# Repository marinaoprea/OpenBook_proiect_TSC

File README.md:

### ESP32-C6 pin connections
* 3V3 - charging 3V3
* EN - Reset button
* IO0 - pin for communication with the RTC (to get alert or timing signals)
* IO1 - pin used to communicate with the RTC to get a stable clock reference
* IO2 - used for SPI (Master In Slave Out)
* IO3 - used to connect to display, indicates the display's busy status
* IO4 - used to communicate with the SD card
* IO5 - used to connect to the display, distinguishes between data and command signals sent to
        to the display
* IO6 - used for SPI communication, synchronizes data transfer
* IO7 - used for SPI (Master Out Slave In)
* IO8 - not used
* IO9 - Boot button
* IO10 - used to connect to the display, selects the display for communication
* IO11 - selects the flash memory for communication
* IO12 - D+ for USB connection
* IO13 - D- for USB connection
* IO15 - Change button
* TXd0 / GPIO16 - used for UART debugging
* RXD0/GPIO17 - used for UART debugging
* IO18 - resets RTC
* IO19 - power pin for I2C communication
* IO20 - power for display
* IO21 - used for I2C, data pin
* IO22 - used for I2C, clock pin
* IO23 - resets display
* GND - connected to GND

### Bill of Materials

| Part | Value | Datasheet Link | Buy Link
|:------|:-------|:----------------|:---------------|
| BOOT_BUTTON | BUTTON_CUSYOMV1 | [Datasheet](https://www3.panasonic.biz/ac/e_download/control/switch/light-touch/catalog/sw_lt_eng_6s_th.pdf?f_cd=402892) | [Buy](https://ro.mouser.com/ProductDetail/Panasonic/EVQ-PUJ02K?qs=Pa1bP%252BeMzadWe338tXJdGA%3D%3D&utm_id=6470900573&utm_source=google&utm_medium=cpc&utm_marketing_tactic=emeacorp&gad_source=1&gclid=CjwKCAjwzMi_BhACEiwAX4YZULlhUyQwmA3c7mdDUuSFCAo9XeR8UBKFF0gyZe49KYTmnIC5sRRx0RoCqN8QAvD_BwE)
| C1 | 100nF | [Datasheet](https://ro.mouser.com/datasheet/2/447/KEM_C1006_X5R_SMD-3316465.pdf) | [Buy](https://ro.mouser.com/ProductDetail/YAGEO/CC0402MRX5R5BB106?qs=zEY9bCHj09eCmUJdZuS5Lg%3D%3D&utm_id=6470900573&utm_source=google&utm_medium=cpc&utm_marketing_tactic=emeacorp&gad_source=1&gclid=CjwKCAjwzMi_BhACEiwAX4YZUH3AaP6uvHGdYeUYb7BO2eMjk8ZR0XihcHuw-sWwNUHwSShuLip--hoCBnYQAvD_BwE)
| C1_BAT | 4.7uF | [Datasheet](https://ro.mouser.com/datasheet/2/447/KEM_C1006_X5R_SMD-3316465.pdf) | [Buy](https://ro.mouser.com/ProductDetail/YAGEO/CC0402MRX5R5BB106?qs=zEY9bCHj09eCmUJdZuS5Lg%3D%3D&utm_id=6470900573&utm_source=google&utm_medium=cpc&utm_marketing_tactic=emeacorp&gad_source=1&gclid=CjwKCAjwzMi_BhACEiwAX4YZUH3AaP6uvHGdYeUYb7BO2eMjk8ZR0XihcHuw-sWwNUHwSShuLip--hoCBnYQAvD_BwE)
| C1_BAT1 | 4.7uF |  |
| C1_BAT2 | 4.7uF |  |
| C2 | 100nF |  |
| C2_BAT | 4.7uF |  |
| C3 | 100uF TANT |  |
| C4 | 4.7uF/25V |  |
| C4_USB | 100nF |  |
| C5 | 1uF |  |
| C5_USB | 4.7uF |  |
| C6 | 100nF |  |
| C7 | 10uF |  |
| C8 | 100nF |  |
| C9 | 100nF |  |
| C10 | 100nF |  |
| C10_SUPERCAP | | [Datasheet](https://www.snapeda.com/parts/CPH3225A/Seiko+Instruments/view-part/?ref=eda) | [Buy](https://www.digikey.ro/en/products/detail/seiko-instruments/CPH3225A/8692444?utm_campaign=buynow&utm_medium=aggregator&utm_source=snapeda)
| CHANGE_BUTTON BUTTON_CUSYOMV1 | |  |
| CHG_LED | |[Datasheet](https://dammedia.osram.info/media/resource/hires/osram-dam-14795755/LG%20R971_EN.pdf) | [Buy](https://www.arrow.com/en/products/kp-1608surck/kingbright?utm_campaign=arrow_snapeda_q32020&utm_currency=USD&utm_term=KP-1608SURCK&utm_content=inpart_link_download&region=europe&utm_source=snapeda&utm_medium=aggregator)
| C_DELAY | 100nF |  |
| D1 | | [Datasheet](https://www.snapeda.com/parts/USBLC6-2SC6Y/STMicroelectronics/view-part/?ref=eda) | [Buy](https://www.digikey.ro/en/products/detail/stmicroelectronics/USBLC6-2SC6Y/2756523?utm_source=findchips&utm_medium=aggregator&utm_campaign=buynow)
| D2 |  |  |
| D3 |  | [Datasheet](https://www.snapeda.com/parts/MBR0530/Onsemi/view-part/?ref=eda) | [Buy](https://www.digikey.ro/en/products/detail/smc-diode-solutions/MBR0530/16692306)
| D4 | | [Datasheet](https://www.snapeda.com/parts/MBR0530/Onsemi/view-part/?ref=eda) |
| D5 |  | [Datasheet](https://www.snapeda.com/parts/MBR0530/Onsemi/view-part/?ref=eda) |
| D6 |  | [Datasheet](https://www.snapeda.com/parts/PGB1010603MR/Littelfuse/view-part/?ref=eda) |
| D7 |  |  |
| D8 |  | [Datasheet](https://www.snapeda.com/parts/PGB1010603MR/Littelfuse/view-part/?ref=eda) | [Buy](https://www.digikey.ro/en/products/detail/littelfuse-inc/PGB1010603MR/715755?utm_campaign=buynow&utm_medium=aggregator&utm_source=snapeda)
| D9 || [Datasheet](https://www.snapeda.com/parts/PGB1010603MR/Littelfuse/view-part/?ref=eda) |
| D10 |  | [Datasheet](https://www.snapeda.com/parts/PGB1010603MR/Littelfuse/view-part/?ref=eda) |
| D11 |  | [Datasheet](https://www.snapeda.com/parts/PGB1010603MR/Littelfuse/view-part/?ref=eda) |
| D12 |  | [Datasheet](https://www.snapeda.com/parts/PGB1010603MR/Littelfuse/view-part/?ref=eda) |
| EPD_C1 | 1uF/50V | [Datasheet](https://ro.mouser.com/datasheet/2/396/TDK_4_24_2024_MAASU32NSB7105KTCA01_SS-3440852.pdf) |
| EPD_C2 | 1uF/50V |  |
| EPD_C5 | 1uF/50V |  |
| EPD_C6 | 1uF/50V |  |
| EPD_C7 | 1uF/50V |  |
| EPD_C8 | 1uF/50V |  |
| EPD_C9 | 1uF/50V |  |
| EPD_C10 | 1uF/50V |  |
| EPD_C11 | 1uF/50V |  |
| EPD_C12 | 1uF/50V |  |
| IC2 |  | [Datasheet](https://datasheet.datasheetarchive.com/originals/distributors/Datasheets_SAMA/f2b9741ef86007909f138d561a359946.pdf) | [Buy](https://www.digikey.ro/en/products/detail/rohm-semiconductor/BD5229G-TR/3663792?utm_source=findchips&utm_medium=aggregator&utm_campaign=buynow)
| IC4 | | [Datasheet](https://www.torexsemi.com/file/xc6220/XC6220.pdf) | [Buy](https://www.digikey.ro/en/products/detail/torex-semiconductor-ltd/XC6220A331MR-G/21780806?utm_source=findchips&utm_medium=aggregator&utm_campaign=buynow)
| J1 |  | [Datasheet](https://www.hirose.com/en/product/document?clcode=CL0580-1255-6-99&productname=FH34SRJ-24S-0.5SH(99)&series=FH34SRJ&documenttype=2DDrawing&lang=en&documentid=0000990903) | [Buy](https://www.digikey.ro/en/products/detail/hirose-electric-co-ltd/FH34SRJ-24S-0.5SH(99)/5156248?utm_source=findchips&utm_medium=aggregator&utm_campaign=buynow)
| J2 | | [Datasheet](https://gct.co/files/drawings/usb4110.pdf) | [Buy](https://ro.mouser.com/ProductDetail/GCT/USB4110-GF-A?qs=KUoIvG%2F9IlYiZvIXQjyJeA%3D%3D&utm_source=findchips&utm_medium=aggregator&utm_campaign=USB4110-GF-A&utm_term=USB4110-GF-A&utm_content=GCT&_gl=1*az782z*_ga*MTIzOTk3MzcxNi4xNzQzNzg3ODcx*_ga_15W4STQT4T*MTc0Mzk1MTg1Ny43LjEuMTc0Mzk1MzM0NS4zNy4wLjA.)
| J3 |  | [Datasheet](https://cdn-shop.adafruit.com/product-files/4208/4208_Kaweei_C13396_diagram.pdf) | [Buy](https://ro.mouser.com/ProductDetail/JST-Commercial/SM04B-SRSS-TBLFSN?utm_campaign=mouser&qs=cdbOS8ANM9B3FdyA6cNU2A==&utm_medium=online&utm_source=snapedaonline&utm_content=model)
| J4 | | [Datasheet](https://www.attend.com.tw/data/download/file/112A-TAAR-R03.pdf) | [Buy](https://www.digikey.ro/en/products/detail/attend-technology/112A-TAAR-R03/17633923?utm_source=findchips&utm_medium=aggregator&utm_campaign=buynow)
| L1 | 68uH | [Datasheet](https://ro.mouser.com/datasheet/2/390/CR75-514217.pdf) | [Buy](https://www.chip1stop.com/USA/en/products/Wurth-Electronics/744043680/WURT*0001522?aacpc=findchips_inv_listing&utm_campaign=c1sapac_findchips_2025&utm_medium=aggregator&utm_source=findchips&utm_content=inv_listing)
| PFMF.050.1 | ESP32C6_VARISTORCN1812 | [Datasheet](www.farnell.com/datasheets/49238.pdf) | [Buy](https://ro.mouser.com/ProductDetail/EPCOS-TDK/B72520T0350K062?qs=dEfas%2FXlABIszF52uu7vrg%3D%3D&utm_source=findchips&utm_medium=aggregator&utm_campaign=B72520T0350K062&utm_term=B72520T0350K062&utm_content=TDK)
| Q1 | 20V/4.2A/52m?/1.4W | [Datasheet](https://www.diodes.com/assets/Datasheets/DMG2305UX.pdf) | [Buy](https://www.digikey.ro/en/products/detail/diodes-incorporated/DMG2305UX-7/4340666?utm_source=findchips&utm_medium=aggregator&utm_campaign=buynow)
| Q2 | 20V/4.2A/52m?/1.4W |  |
| R1 | 10K | [Datasheet](https://www.vishay.com/doc?20037) | [Buy](https://ro.mouser.com/ProductDetail/YAGEO/RC0402FR-07100KL?qs=mnq%2FyloZIXzTlUn7JAHSWg%3D%3D)|
| R1_BAT | 200 | [Datasheet](https://www.vishay.com/doc?60057) |
| R1_PINH | 10K |  |
| R1_PINH1 | 10K |  |
| R1_PWRUSB | 100K | [Datasheet](https://ro.mouser.com/datasheet/2/414/TTRB_S_A0010186342_1-2565648.pdf) |
| R2 | 2.2 |  |
| R2-PINH1 | 10K |  |
| R2-USB | 5k1 | [Datasheet](https://www.vishay.com/doc?20008) |
| R2-USB1 | 5k1 |  |
| R2_BAT | 2K |  |
| R2_PINH | 10K |  |
| R3 | 0.47 |  |
| R4 | 10K |  |
| R5 | 10K |  |
| R6 | 10K |  |
| R7 | 10K |  |
| R8 | 10K |  |
| R9 | 10K |  |
| R10 | 10K |  |
| RESET_BUTTON | BUTT |  |
| R_BOOT | 10K |  |
| R_CAPACITOR | 15 |  |
| R_CHANGE | 10K |  |
| R_CL1 | 10K |  |
| R_RESET | 10K |  |
| SJ1 | |  |
| U1 | | [Datasheet](https://www.snapeda.com/parts/ESP32-C6-WROOM-1-N8/Espressif+Systems/view-part/?ref=eda) | [Buy](https://www.digikey.ro/en/products/detail/espressif-systems/ESP32-C6-WROOM-1-N8/17728866?utm_campaign=buynow&utm_medium=aggregator&utm_source=snapeda)
| U2 |  | [Datasheet](https://ro.mouser.com/datasheet/2/268/MCP73831_Family_Data_Sheet_DS20001984H-3441711.pdf) | [Buy](https://ro.mouser.com/ProductDetail/Microchip-Technology/MCP73831T-2ACI-OT?qs=yUQqVecv4qvbBQBGbHx0Mw%3D%3D)
| U3 | | [Datasheet](https://ro.mouser.com/datasheet/2/609/DS3231-3421123.pdf) | [Buy](https://www.digikey.ro/en/products/detail/analog-devices-inc-maxim-integrated/DS3231SN/1197576?utm_campaign=buynow&utm_medium=aggregator&utm_source=snapeda)
| U4 | | [Datasheet](https://www.snapeda.com/parts/MAX17048G+T10/Analog+Devices/view-part/?ref=eda) | [Buy](https://www.digikey.ro/en/products/detail/analog-devices-inc-maxim-integrated/MAX17048G-T10/3758921?utm_campaign=buynow&utm_medium=aggregator&utm_source=snapeda)
| U5 |  | [Datasheet](https://www.snapeda.com/parts/W25Q512JVEIQ/Winbond+Electronics/view-part/?ref=eda) | [Buy](https://www.digikey.ro/en/products/detail/winbond-electronics/W25Q512JVEIQ/10244706?utm_campaign=buynow&utm_medium=aggregator&utm_source=snapeda)
| U6 |  | [Datasheet](https://ro.mouser.com/datasheet/2/783/BST_BME680_DS001-1509608.pdf) | [Buy](https://www.digikey.ro/en/products/detail/bosch-sensortec/BME680/7401317?utm_campaign=buynow&utm_medium=aggregator&utm_source=snapeda)

## Block diagram

## System Overview

This project integrates various components to create a versatile and efficient system with multiple functionalities.

## Components

### ESP32-C6-WROOM-1-N8 Microcontroller
- Serves as the central processing unit, managing all communication and control.
- Supports **Wi-Fi**, **Bluetooth**, **Zigbee**, and **Thread** for wireless communication.

### RTC Module (DS3231SN)
- Maintains accurate timekeeping and provides time/date information via the **I2C protocol**.

### Flash Memory (W25Q512JVEIQ)
- Provides high-speed storage using the **SPI protocol**
- Used for firmware and data storage

### Battery Management IC (MCP73831)
- Handles charging of the Li-Ion battery with input from the USB Type-C port.
- GPIO pins monitor charging status and control power management.

### Fuel Gauge IC (MAX17048G+T10)
- Tracks the battery's state of charge and communicates with the microcontroller using **I2C protocol**.

### Environmental Sensor (BME680)
- Monitors temperature, humidity, pressure, and gas levels.
- Connects via the **I2C protocol**.

### ePaper Display
- Displays information to the user.
- Interfaced using the **SPI protocol** for fast data updates.

### SD Card Socket (J4)
- Provides expandable storage for data logging or firmware updates.
- Communicates using the **SPI protocol**.

### USB Type-C Port (J2)
- Supplies power to the system and enables communication with external devices.
- Includes **D+** and **D−** lines for USB data transfer.

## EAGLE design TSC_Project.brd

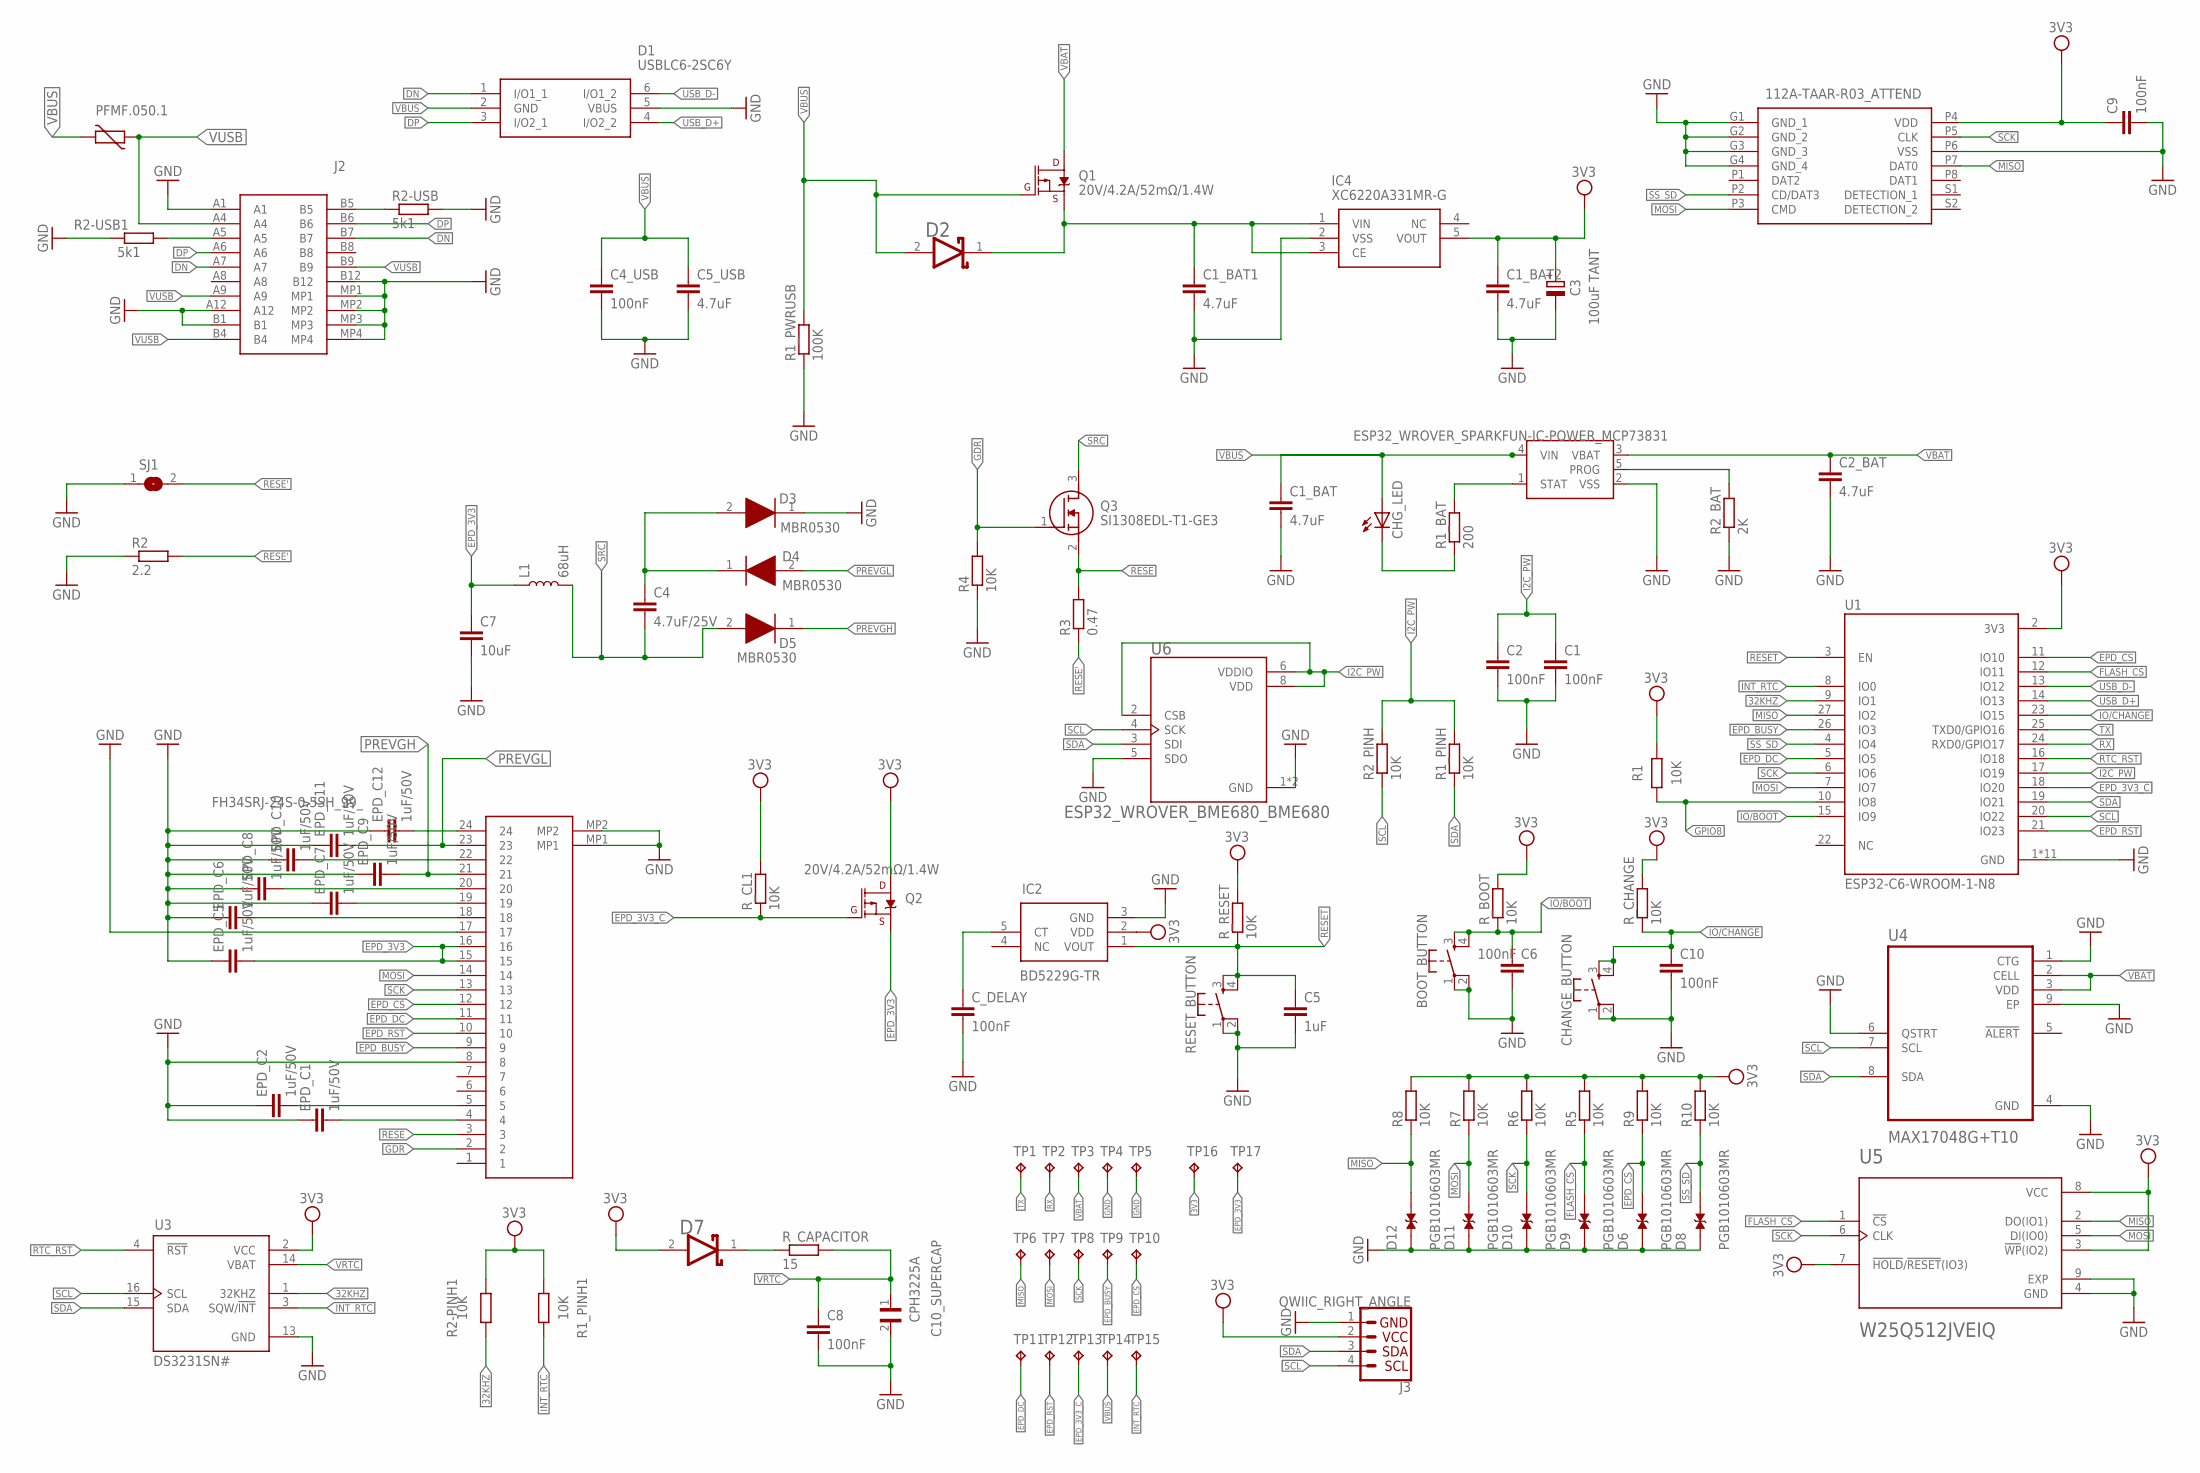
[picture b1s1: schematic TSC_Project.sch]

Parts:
BOOT_BUTTON: BUTTON_CUSYOMV1; MYBUTTON
C1, C2, C6, C8, C9, C10: 100nF; ESP32_WROVER_EAGLE-LTSPICE_C0402
C1_BAT, C2_BAT: 4.7uF; ESP32_WROVER_EAGLE-LTSPICE_C0402
C1_BAT1, C1_BAT2, C5_USB: 4.7uF; EAGLE-LTSPICE_C0402
C3: 100uF TANT; RCL_CT3528
C4: 4.7uF/25V; ESP32_WROVER_EAGLE-LTSPICE_C0402
C4_USB: 100nF; EAGLE-LTSPICE_C0402
C5: 1uF; ESP32_WROVER_EAGLE-LTSPICE_C0402
C7: 10uF; ESP32_WROVER_EAGLE-LTSPICE_C0402
C10_SUPERCAP: CPH3225A; CAPCP3225X100N
CHANGE_BUTTON: BUTTON_CUSYOMV1; MYBUTTON
CHG_LED: ADAFRUIT_LEDCHIP-LED0603; ADAFRUIT_CHIP-LED0603
C_DELAY: 100nF; EAGLE-LTSPICE_C0402
D1: USBLC6-2SC6Y; SOT95P280X145-6N
D2, D7: ESP32_WROVER_AVX---SD0805S020S1R0_AVX_SD0805S020S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; ESP32_WROVER_AVX---SD0805S020S1R0_AVX_SD0805S020S1R0_0
D3, D4, D5: MBR0530; SOD3716X135N
D6, D8, D9, D10, D11, D12: PGB1010603MR; DIOC1608X36N
EPD_C1, EPD_C2, EPD_C5, EPD_C6, EPD_C7, EPD_C8, EPD_C9, EPD_C10, EPD_C11, EPD_C12: 1uF/50V; ESP32_WROVER_EAGLE-LTSPICE_C0402
IC2: BD5229G-TR; SOT95P280X125-5N
IC4: XC6220A331MR-G; SOT95P280X120-5N
J1: FH34SRJ-24S-0.5SH_99_; FH34SRJ24S05SH99
J2: SAMACSYS_PARTS_USB4110-GF-A; SAMACSYS_PARTS_USB4110GFA
J3: QWIIC_RIGHT_ANGLE; JST04_1MM_RA
J4: 112A-TAAR-R03_ATTEND; 112ATAARR03ATTEND
L1: 68uH; CR75
PFMF.050.1: ESP32C6_VARISTORCN1812; ESP32C6_VARISTOR_CT/CN1812
Q1, Q2: 20V/4.2A/52mΩ/1.4W; ESP32_WROVER_SPARKFUN-DISCRETESEMI_SOT23-3
Q3: SI1308EDL-T1-GE3; SOT65P210X110-3N
R1, R1_PINH, R1_PINH1, R2-PINH1, R2_PINH, R4, R5, R6, R7, R8, R9, R10: 10K; ESP32_WROVER_EAGLE-LTSPICE_R0402
R1_BAT: 200; ESP32_WROVER_EAGLE-LTSPICE_R0402
R1_PWRUSB: 100K; ESP32_WROVER_EAGLE-LTSPICE_R0402
R2: 2.2; ESP32_WROVER_EAGLE-LTSPICE_R0402
R2-USB, R2-USB1: 5k1; ESP32_WROVER_EAGLE-LTSPICE_R0402
R2_BAT: 2K; ESP32_WROVER_EAGLE-LTSPICE_R0402
R3: 0.47; ESP32_WROVER_EAGLE-LTSPICE_R0402
RESET_BUTTON: BUTTON_CUSYOMV1; MYBUTTON
R_BOOT: 10K; ESP32_WROVER_EAGLE-LTSPICE_R0402
R_CAPACITOR: 15; ESP32_WROVER_EAGLE-LTSPICE_R0402
R_CHANGE: 10K; ESP32_WROVER_EAGLE-LTSPICE_R0402
R_CL1: 10K; ESP32_WROVER_EAGLE-LTSPICE_R0402
R_RESET: 10K; ESP32_WROVER_EAGLE-LTSPICE_R0402
SJ1: SJ
TP1, TP2, TP3, TP4, TP5, TP6, TP7, TP8, TP9, TP10, TP11, TP12, TP13, TP14, TP15, TP16, TP17: TPTP20R; TP20R
U1: ESP32-C6-WROOM-1-N8; XCVR_ESP32-C6-WROOM-1-N8
U2: ESP32_WROVER_SPARKFUN-IC-POWER_MCP73831; ESP32_WROVER_SPARKFUN-IC-POWER_SOT23-5
U3: DS3231SN#; SOIC127P1032X265-16N
U4: MAX17048G+T10; SON50P200X200X80-9N
U5: W25Q512JVEIQ; SON127P600X800X80-9N
U6: ESP32_WROVER_BME680_BME680; ESP32_WROVER_BME680_PSON80P300X300X100-8N

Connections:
3V3: C1_BAT2.1, C3.+, C9.1, D7.2 (ANODE), IC2.2 (VDD), IC4.5 (VOUT), J3.2, J4.P4 (VDD), Q2.3 (D), R1.2, R1_PINH1.2, R2-PINH1.2, R5.2, R6.2, R7.2, R8.2, R9.2, R10.2, R_BOOT.2, R_CHANGE.2, R_CL1.2, R_RESET.2, TP16.TP, U1.2 (3V3), U3.2 (VCC), U5.3 (!WP!(IO2)), U5.7 (!HOLD!/!RESET!(IO3)), U5.8 (VCC)
32KHZ: R2-PINH1.1, U1.9 (IO1), U3.1 (32KHZ)
DN: D1.1 (I/O1_1), J2.A7, J2.B7
DP: D1.3 (I/O2_1), J2.A6, J2.B6
EPD_3V3: C7.1, EPD_C5.2, J1.15, J1.16, L1.P$1 (1), Q2.2 (S), TP17.TP
EPD_3V3_C: Q2.1 (G), R_CL1.1, TP13.TP, U1.18 (IO20)
EPD_BUSY: J1.9, TP9.TP, U1.26 (IO3)
EPD_CS: D6.2, J1.12, R9.1, TP10.TP, U1.11 (IO10)
EPD_DC: J1.11, TP11.TP, U1.5 (IO5)
EPD_RST: J1.10, TP12.TP, U1.21 (IO23)
FLASH_CS: D9.2, R5.1, U1.12 (IO11), U5.1 (!CS)
GDR: J1.2, Q3.1 (G), R4.2
GND: BOOT_BUTTON.1, BOOT_BUTTON.2, C1.2, C1_BAT.2, C1_BAT1.2, C1_BAT2.2, C2.2, C2_BAT.2, C3.-, C4_USB.2, C5.2, C5_USB.2, C6.2, C7.2, C8.2, C9.2, C10.2, C10_SUPERCAP.2, CHANGE_BUTTON.1, CHANGE_BUTTON.2, C_DELAY.2, D1.5 (VBUS), D3.1 (K), D6.1, D8.1, D9.1, D10.1, D11.1, D12.1, EPD_C1.1, EPD_C2.1, EPD_C5.1, EPD_C6.1, EPD_C7.1, EPD_C8.1, EPD_C9.1, EPD_C10.1, EPD_C11.1, EPD_C12.1, IC2.3 (GND), IC4.2 (VSS), J1.8, J1.17, J1.MP1, J1.MP2, J2.A1, J2.A12, J2.B1, J2.B12, J2.MP1, J2.MP2, J2.MP3, J2.MP4, J3.1, J4.G1 (GND_1), J4.G2 (GND_2), J4.G3 (GND_3), J4.G4 (GND_4), J4.P6 (VSS), R1_PWRUSB.1, R2.1, R2-USB.2, R2-USB1.1, R2_BAT.1, R4.1, RESET_BUTTON.1, RESET_BUTTON.2, SJ1.1, TP4.TP, TP5.TP, U1.1 (GND), U1.28 (GND), U1.29_1 (GND), U1.29_2 (GND), U1.29_3 (GND), U1.29_4 (GND), U1.29_5 (GND), U1.29_6 (GND), U1.29_7 (GND), U1.29_8 (GND), U1.29_9 (GND), U2.2 (VSS), U3.13 (GND), U4.1 (CTG), U4.4 (GND), U4.6 (QSTRT), U4.9 (EP), U5.4 (GND), U5.9 (EXP), U6.1 (GND), U6.5 (SDO), U6.7 (GND)
GPIO8: R1.1, U1.10 (IO8)
I2C_PW: C1.1, C2.1, R1_PINH.2, R2_PINH.2, U1.17 (IO19), U6.2 (CSB), U6.6 (VDDIO), U6.8 (VDD)
INT_RTC: R1_PINH1.1, TP15.TP, U1.8 (IO0), U3.3 (SQW/!INT)
IO/BOOT: BOOT_BUTTON.3, BOOT_BUTTON.4, C6.1, R_BOOT.1, U1.15 (IO9)
IO/CHANGE: C10.1, CHANGE_BUTTON.3, CHANGE_BUTTON.4, R_CHANGE.1, U1.23 (IO15)
MISO: D12.2, J4.P7 (DAT0), R8.1, TP6.TP, U1.27 (IO2), U5.2 (DO(IO1))
MOSI: D11.2, J1.14, J4.P3 (CMD), R7.1, TP7.TP, U1.7 (IO7), U5.5 (DI(IO0))
unnamed: EPD_C12.2, J1.24
unnamed: R1_BAT.2, U2.1 (STAT)
unnamed: CHG_LED.C, R1_BAT.1
unnamed: D7.1 (CATHODE), R_CAPACITOR.1
unnamed: J2.A5, R2-USB1.2
unnamed: J2.B5, R2-USB.1
unnamed: R2_BAT.2, U2.5 (PROG)
unnamed: EPD_C1.2, J1.4
unnamed: C1_BAT1.1, D2.1 (CATHODE), IC4.1 (VIN), IC4.3 (CE), Q1.2 (S)
unnamed: EPD_C2.2, J1.5
unnamed: C4.1, D3.2 (A), D4.1 (K)
unnamed: EPD_C6.2, J1.18
unnamed: EPD_C7.2, J1.19
unnamed: EPD_C8.2, J1.20
unnamed: C_DELAY.1, IC2.5 (CT)
unnamed: EPD_C10.2, J1.22
PREVGH: D5.1 (K), EPD_C9.2, J1.21
PREVGL: D4.2 (A), EPD_C11.2, J1.23
RESE: J1.3, Q3.2 (S), R3.2
RESE': R2.2, R3.1, SJ1.2
RESET: C5.1, IC2.1 (VOUT), RESET_BUTTON.3, RESET_BUTTON.4, R_RESET.1, U1.3 (EN)
RTC_RST: U1.16 (IO18), U3.4 (!RST)
RX: TP2.TP, U1.24 (RXD0/GPIO17)
SCK: D10.2, J1.13, J4.P5 (CLK), R6.1, TP8.TP, U1.6 (IO6), U5.6 (CLK)
SCL: J3.4, R2_PINH.1, U1.20 (IO22), U3.16 (SCL), U4.7 (SCL), U6.4 (SCK)
SDA: J3.3, R1_PINH.1, U1.19 (IO21), U3.15 (SDA), U4.8 (SDA), U6.3 (SDI)
SRC: C4.2, D5.2 (A), L1.P$2 (2), Q3.3 (D)
SS_SD: D8.2, J4.P2 (CD/DAT3), R10.1, U1.4 (IO4)
TX: TP1.TP, U1.25 (TXD0/GPIO16)
USB_D+: D1.4 (I/O2_2), U1.14 (IO13)
USB_D-: D1.6 (I/O1_2), U1.13 (IO12)
VBAT: C2_BAT.1, Q1.3 (D), TP3.TP, U2.3 (VBAT), U4.2 (CELL), U4.3 (VDD)
VBUS: C1_BAT.1, C4_USB.1, C5_USB.1, CHG_LED.A, D1.2 (GND), D2.2 (ANODE), PFMF.050.1.2, Q1.1 (G), R1_PWRUSB.2, TP14.TP, U2.4 (VIN)
VRTC: C8.1, C10_SUPERCAP.1, R_CAPACITOR.2, U3.14 (VBAT)
VUSB: J2.A4, J2.A9, J2.B4, J2.B9, PFMF.050.1.1

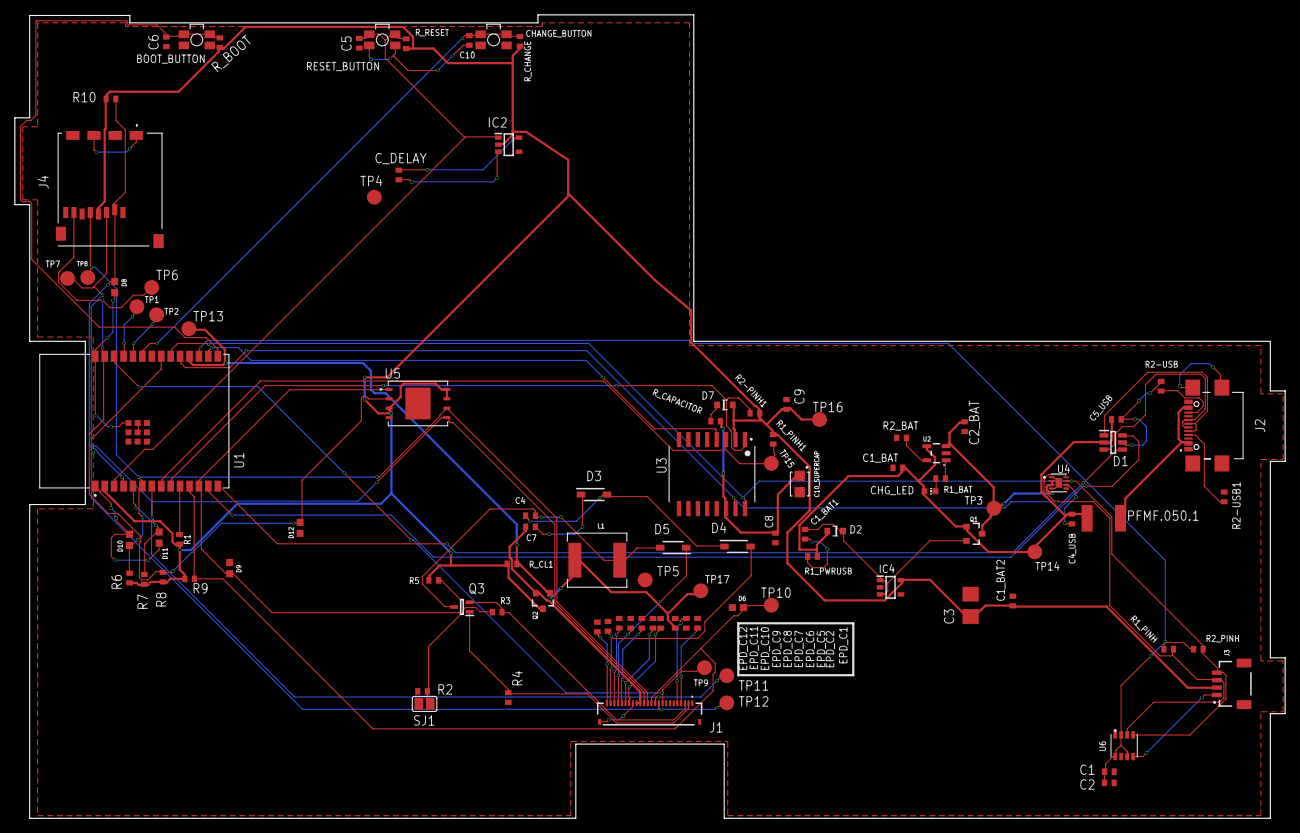
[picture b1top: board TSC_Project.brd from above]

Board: 2 copper layers, 171.2 x 108.3 mm, 103 parts (0 on the bottom side), 55 nets.

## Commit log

2025-03-24 Create LICENSE
2025-03-24 Added .sch and .brd
2025-03-24 Added first draft of readme
2025-04-05 Added files .sch and .brd
2025-04-05 Create file
2025-04-13 Replaced block diagram
2025-04-13 included gpio8 purpose
2025-04-13 replaced board images
2025-04-13 Rename boad_left_view.png to board_left_view.png
2025-04-13 replaced .sch and .brd
2025-04-13 Update README.md to contain buy links
2025-04-15 updated f3z file
2025-04-15 update .step and .avi files
2025-04-15 updated .avi path

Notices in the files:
parts and their libraries:
SparkFun-Coils: Licensing: Creative Commons ShareAlike 4.0 International - https://creativecommons.org/licenses/by-sa/4.0
